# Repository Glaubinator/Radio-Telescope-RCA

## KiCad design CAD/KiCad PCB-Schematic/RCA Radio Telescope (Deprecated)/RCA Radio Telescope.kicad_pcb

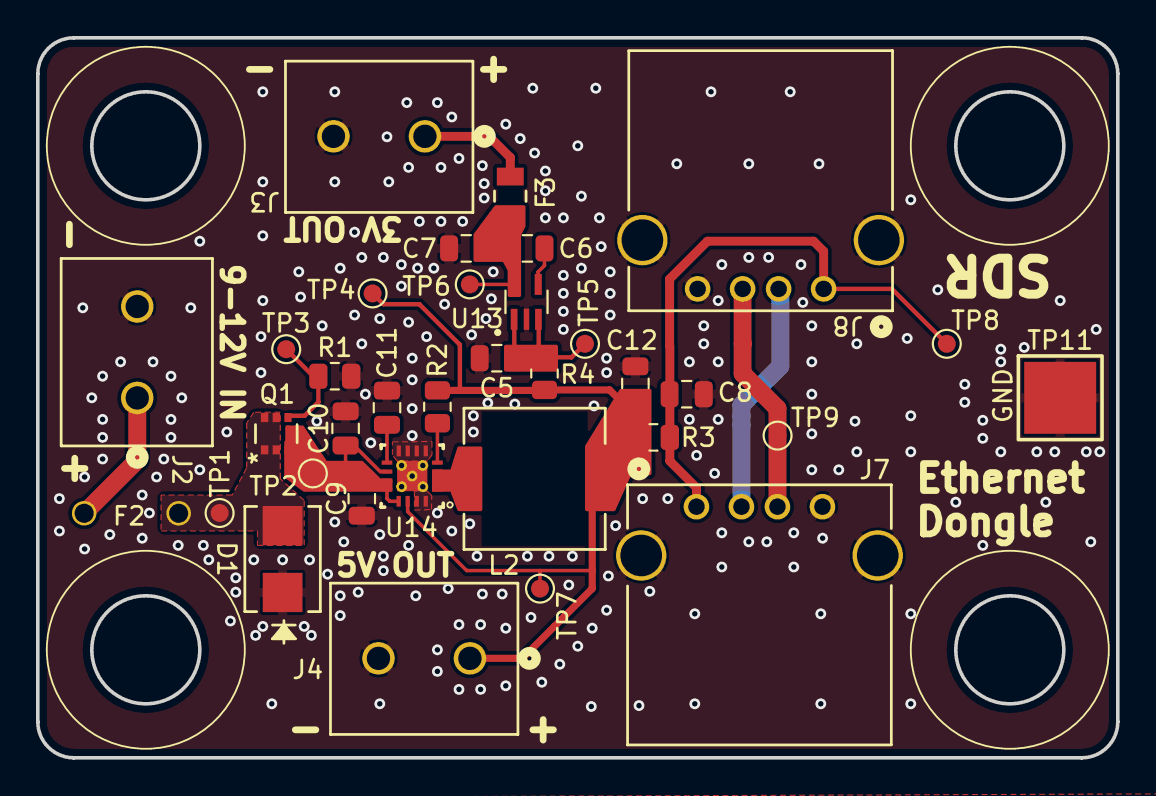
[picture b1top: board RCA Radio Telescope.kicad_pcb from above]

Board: 2 copper layers, 60.0 x 40.0 mm, 35 parts (1 on the bottom side), 16 nets.

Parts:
C5, C7: 1 uF; C_0805_2012Metric
C6: 10 nf; C_0805_2012Metric
C8: 10 uF; C_0805_2012Metric
C9: 10uF; C_0805_2012Metric
C10: 0.1uF; C_0805_2012Metric
C11: 3.3nF; C_0805_2012Metric
C12: 22uF; C_0805_2012Metric
D1: SMBJ12A-13-F; SMB_DIO
F2: RGEF300K-2
F3: 0ZCK0020FF2G; 0ZCK_BEL
J2: 5V From PoE Splitter; CONN_1729128_PXC
J3: 3V Out For LNA; CONN_1729128_PXC
J4: 5V Out For Filter Board; CONN_1729128_PXC
J7, J8: USB_A; CONN_AU-Y1005-2_ASM
L2: 2.2uH; IND_CB_DRA73
Q1: DMP4047LFDE-7; U-DFN2020-6_DIO
R1, R2: 100k; R_0805_2012Metric
R3, R4: 0; R_0805_2012Metric
TP1: PROCTVIN; TestPoint_Pad_D1.0mm_Edit
TP2: 5VBUCKVIN; TestPoint_Pad_D1.0mm_Edit
TP3: G_PMOS; TestPoint_Pad_D1.0mm_Edit
TP4: 5VBUCKVOUT; TestPoint_Pad_D1.0mm_Edit
TP5: 3VLDOIN; TestPoint_Pad_D1.0mm_Edit
TP6: 3VLDOOUT; TestPoint_Pad_D1.0mm_Edit
TP7: 5VOUT; TestPoint_Pad_D1.0mm_Edit
TP8: 5VUSB; TestPoint_Pad_D1.0mm_Edit
TP9: D+USB; TestPoint_Pad_D1.0mm_Edit
TP10: D-USB; TestPoint_Pad_D1.0mm_Edit
TP11: GNDCLIP; TestPoint_Pad_4.0x4.0mm_Edit
U13: MAX8510EXK30T; SOT65P210X110-5N
U14: TPS62133RGTR; RGT0016C

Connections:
+3V0: F3.2, J3.1
+5V: C12.1, J4.1, L2.2, R2.1, R3.2, R4.2, TP4.1, TP7.1, U14.14 (VOS)
/PowerDataDistribute/USB_5V_IN: C8.1, J7.1 (VBUS), J8.1 (VBUS), R3.1, TP8.1
/PowerDataDistribute/USB_D+_IN: J7.3 (D+), J8.3 (D+), TP9.1
/PowerDataDistribute/USB_D-_IN: J7.2 (D-), J8.2 (D-), TP10.1
/PowerDataDistribute/VDD: F2.1, J2.1
GND: C5.2, C7.2, C8.2, C9.2, C10.2, C11.1, C12.2, D1.2, J2.2, J3.2, J4.2, J7.4 (GND), J8.4 (GND), R1.2, TP11.1, U13.2 (GND), U14.5 (FB), U14.6 (AGND), U14.7 (FSW), U14.8 (DEF), U14.15 (PGND), U14.16 (PGND), U14.17 (EP), U14.18, U14.19, U14.20, U14.21, U14.22
unnamed: L2.1, U14.1 (SW), U14.2 (SW), U14.3 (SW)
unnamed: D1.1, F2.2, Q1.1 (D), TP1.1
unnamed: Q1.2 (G), R1.1, TP3.1
unnamed: C9.1, C10.1, Q1.3 (S), TP2.1, U14.10 (AVIN), U14.11 (PVIN), U14.12 (PVIN), U14.13 (EN)
unnamed: C6.2, U13.4 (BP)
unnamed: C5.1, R4.1, TP5.1, U13.1 (IN), U13.3 (~SHDN)
unnamed: C6.1, C7.1, F3.1, TP6.1, U13.5 (OUT)
unnamed: R2.2, U14.4 (PG)
unnamed: C11.2, U14.9 (SS_TR)

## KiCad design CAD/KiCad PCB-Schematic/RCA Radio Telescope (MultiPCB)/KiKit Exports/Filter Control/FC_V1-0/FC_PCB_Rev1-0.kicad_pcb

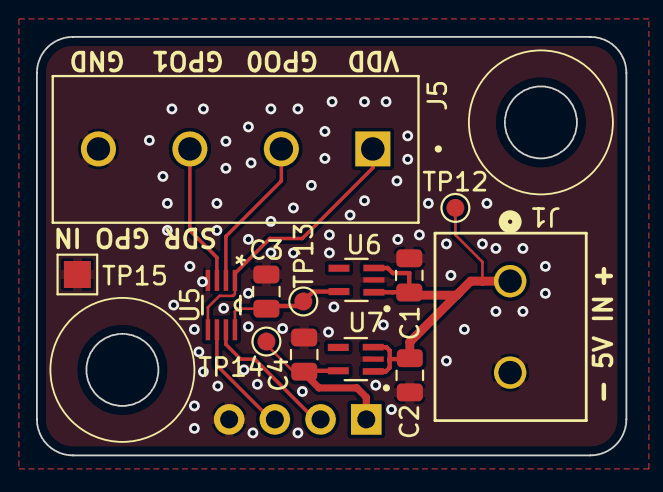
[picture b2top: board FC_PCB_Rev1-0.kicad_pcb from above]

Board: 2 copper layers, 32.8 x 23.2 mm, 15 parts (1 on the bottom side), 9 nets.

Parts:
C1, C2, C3, C4: 1 uF; C_0805_2012Metric
FC: Board
J1: 5V In For Filter Board; CONN_1729128_PXC
J5: Input from SDR; PHOENIX_1729144
J11: Conn_01x04_MountingPin; PinHeader_1x04_P2.54mm_Vertical
TP12, TP13, TP14: TestPoint; TestPoint_Pad_D1.0mm_Edit
TP15: TestPoint; TestPoint_Pad_1.5x1.5mm_Edit
U5: SN74AVC2T45DCUR; DCU8
U6: MIC5365-1.8YC5-TR; SOT65P210X110-5N
U7: MIC5365-3.3YC5-TR; SOT65P210X110-5N

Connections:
/FILTER_GND: C1.2, C2.2, C3.1, C4.1, J1.2, J5.4, J11.4, TP15.1, U5.4 (GND), U6.2 (GND), U7.2 (GND)
/Filters/+3V3: C4.2, J11.1, TP14.1, U7.5 (VOUT)
/Filters/INT_CTRL_V1: J11.2, U5.7 (B1)
/Filters/INT_CTRL_V2: J11.3, U5.6 (B2)
/FiltersCTRL/5V_IN: C1.1, C2.1, J1.1, TP12.1, U6.1 (VIN), U6.3 (EN), U7.1 (VIN), U7.3 (EN)
/FiltersCTRL/+1V8: C3.2, TP13.1, U5.8 (VCCB), U6.5 (VOUT)
/SDR_GPO_0: J5.2, U5.2 (A1)
/SDR_GPO_1: J5.3, U5.3 (A2)
/SDR_GPO_VDD: J5.1, U5.1 (VCCA), U5.5 (DIR)

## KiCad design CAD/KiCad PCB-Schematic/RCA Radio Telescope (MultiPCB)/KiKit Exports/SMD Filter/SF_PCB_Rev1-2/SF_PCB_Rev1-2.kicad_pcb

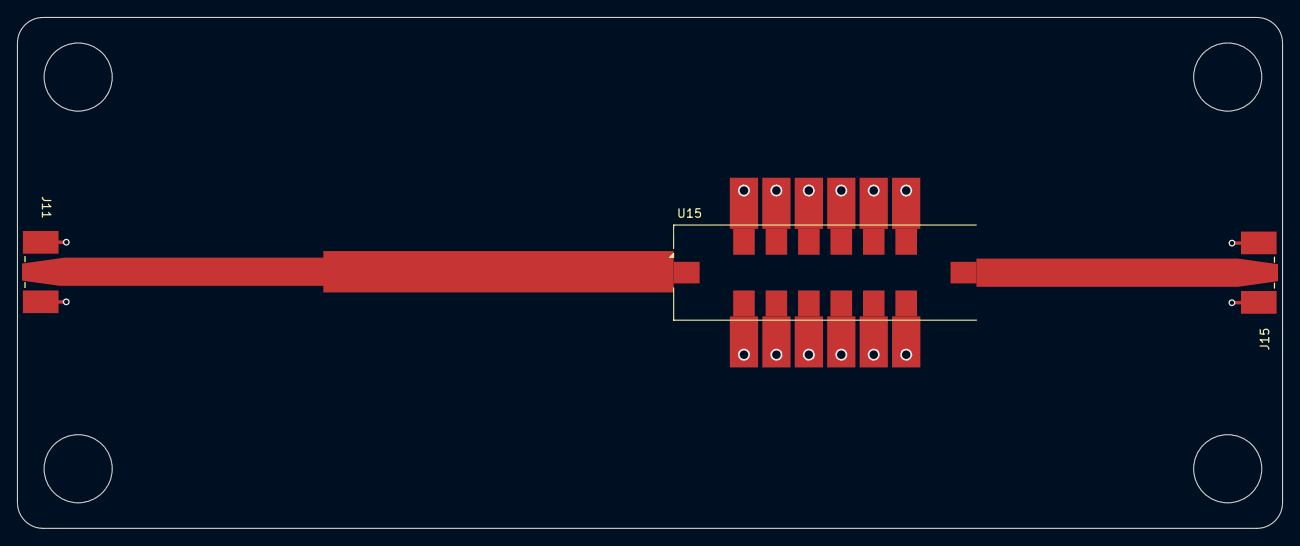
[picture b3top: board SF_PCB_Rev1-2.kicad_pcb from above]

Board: 2 copper layers, 148.6 x 60.0 mm, 4 parts (0 on the bottom side), 3 nets.

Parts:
J11, J15: ANT; CONN_142-0711-821_CIN
SF: Kikit_Board_Label
U15: BPF-A1340+; Mini-Circuits_HQ1157

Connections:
/SMDFilter/GND: J11.3, J11.4, J11.5, J11.6, J15.3, J15.4, J15.5, J15.6, U15.2 (GND), U15.3 (GND), U15.4 (GND), U15.5 (GND), U15.6 (GND), U15.7 (GND), U15.9 (GND), U15.10 (GND), U15.11 (GND), U15.12 (GND), U15.13 (GND), U15.14 (GND)
/SMDFilter/SIGNAL_IN: J11.1 (In), U15.1 (IN)
/SMDFilter/SIGNAL_OUT: J15.1 (In), U15.8 (OUT)
